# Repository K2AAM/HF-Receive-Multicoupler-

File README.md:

# HF Receive Multicoupler — Rev B

One antenna (an active receive loop such as the LZ1AQ AAA-1C or W6LVP) feeding four receivers: an RX888 or RSPdx plus vintage communications receivers. Four ports, through-hole, no hand-wound transformers, 13.8 V supply.

**Status:** design, simulation and a first prototype PCB layout (build A, branch `prototype-pcb`). Nothing here has been built or measured yet. All performance numbers are ngspice simulations with approximate transistor models. Treat them as estimates until the hardware is measured. The second verification pass ([`docs/review2-response.md`](docs/review2-response.md)) lists what is supported, what is not, and what needs bench work.

## Simulated performance, build A (recommended)

Conditions: 50 Ω source, four 50 Ω loads, measured at J2. Nominal parts, 9.81 V rail.

| Parameter | 1 MHz | 7–10 MHz | 28–30 MHz | 50 MHz |
| --- | --- | --- | --- | --- |
| Gain (dB) | +1.72 | +1.69 | +1.42 | +0.84 |
| Port-to-port isolation (dB) | 34.2 | 34.0 | 32.3 | 29.4 |
| Output-to-input isolation (dB) | 107 | 80 | 61 | 52 |
| NF (dB, excludes the receiver's own load noise) | 8.2 | 8.3 | 9.2 | 10.6 |
| IIP3 (dBm, −10 dBm tones) | +32.0 | +30.9 (7 MHz) | +27.1 (28 MHz) | — |

**Other figures:**

- **Flatness:** 0.88 dB from 10 kHz to 50 MHz (gain 1.72 dB at 10 kHz down to 0.84 dB at 50 MHz); 0.3 dB to 30 MHz.
- **Match:** S11 ≤ −23.3 dB and S22 ≤ −23.3 dB from 10 kHz to 50 MHz.
- **FM rejection:** 34.8 dB at 88 MHz, 44.8 dB at 100 MHz, 50.7 dB at 108 MHz.
- **IIP2:** about +79 dBm (6 + 7 MHz) and +79 to +82 dBm (0.6 + 1.0 MHz).
- **Output P1dB:** +11.7 dBm at 7 MHz.
- **Supply:** 95 mA from 13.8 V.

**Tolerance spread** (200-run Monte Carlo, every part independent, published tolerances, LPF inductors VNA-selected to ±3 %):

- gain at 1 MHz: 1.54–1.89 dB
- gain at 50 MHz: 0.69–1.04 dB
- flatness, 10 kHz–50 MHz: 0.79–0.91 dB
- worst S11: −19.4 dB (about −19.2 dB with the stocked ±5 % 43 pF end capacitors now in the BOM)
- rejection at 88 MHz: 33.4–35.8 dB
- NF at 10 MHz: 8.1–9.1 dB
- IIP3 at 7 MHz: +29.1 to +31.8 dBm
- IIP2: +60 to +88 dBm (depends on NPN/PNP matching)
- rail current: 79–97 mA

**If you skip inductor selection,** expect S11 as poor as about −11 dB, flatness up to ~1.3 dB and 88 MHz rejection down to ~31 dB.

All band-edge and named-frequency values come from exact single-frequency solves, not from the nearest sweep point (see section 0 of the review 2 response).

Builds B (+3.2 dB) and C (+5.5 dB) are in [`sim/results/summary.json`](sim/results/summary.json). Build C loses intercept quickly with signals near 0 dBm.

## Prototype PCB (build A)

- **Board:** 2 layers, through-hole, 104 × 78 mm, for a Hammond 1590C.
- **Connectors:** four R/A PCB BNC outputs on the front wall; input BNC on the left wall and DC jack on the back wall, both panel-mounted.
- **Checks:** DRC is clean, and the schematic, PCB and simulation netlists agree pin for pin. KiCad's own ERC still needs one run in eeschema (KiCad 7 has no command-line ERC).
- **Layout-parasitic estimate (simulated):** with the estimated trace capacitance, worst S11 moves from −23 dB to about −18 dB. The gain response barely moves.
- **Before ordering:** the enclosure dimensions and connector panel cut-outs still need checking on real parts.

Details: [`docs/pcb-prototype-A.md`](docs/pcb-prototype-A.md).

## Repository layout

| Path | Contents |
| --- | --- |
| `hardware/` | Schematic (`schematic_revB.png/.svg`, generated by `sch_revb.py`); sourced BOM (`BOM_revB.csv`) |
| `docs/review2-response.md` | Current verification status (supersedes parts of `review-response.md`) |
| `docs/bringup-and-test.md` | Inductor selection, power-only test with dummy load, bring-up and bench tests |
| `docs/layout-guidance.md` | PCB layout rules |
| `docs/pcb-prototype-A.md` | Prototype PCB (build A): part and footprint choices, layout, checks done, Hammond 1590C fit and drilling, layout-parasitic estimate, open items before ordering |
| `hardware/kicad/` | KiCad 7 project (schematic, PCB, footprint library), Gerbers and drill, BOM with MPNs and footprints, board and enclosure images, generator and check scripts |
| `sim/scripts/gen.py` | Single netlist generator; builds A/B/C in `BUILDS`; checked simulation runner |
| `sim/spice/*.cir` | Standalone decks for build A (exported by `export_netlists.py`) |
| `sim/results/` | All generated results |

## Running the simulations

Requires ngspice 42 or later and Python 3 with numpy and matplotlib. Run from `sim/scripts`:

```
python3 test_harness.py       # 26 regression checks: failure handling + exact-frequency sampling
python3 run_all.py            # builds A, B, C: op, AC, NF, IP3/IP2 (80 and 160 steps), P1dB -> summary.json
python3 convergence.py        # two-tone timestep / reltol / method study
python3 mc.py 200 200         # Monte Carlo + corners -> mc_A.json
python3 lpf_study.py 100      # LPF tolerance options
python3 stability.py A        # 5-port S-matrix mu test + 33 cable-kick cases (also B, C); then mu_bands.py A
python3 supply.py             # start-up, headroom, rail impedance, ripple bound, fault, dummy load
python3 freq_density.py       # passband extrema vs sweep density (25-400 points/decade)
python3 thermal.py; python3 export_netlists.py; python3 plot.py
```

Every run uses its own temporary directory and is rejected on any of these:

- non-zero exit
- simulator error text
- missing completion marker
- a missing, stale, empty, non-finite or truncated output

Failures are counted and reported, never skipped.

**Name map** (generator → schematic): CIN1 = C1, CBN/CBP = C2/C3, CF1–CF4 = C4–C7, LF1–LF3 = L1–L3, CFB = C8, CLX = C9, RLX = RL, REO1/REO2 = RE3/RE4, RCOL = RC, CO1–CO4 = C10–C13, CRM/CRMP = C14/C15, CU1O = C23.

## Model limits

- **Transistor models:** 2N3904/2N3906 are simplified Gummel-Poon models from the LTspice library. Absolute IP3/IP2 can differ from hardware by several dB, and IP2 depends on device matching.
- **50 MHz gain:** depends on the real collector capacitance. With CJC 40 % higher than modelled, gain at 50 MHz drops to +0.33 dB (1.39 dB flatness).
- **Regulator model:** the LM317 is behavioural, with ideal line rejection and typical dropout.
- **Stability:** checked to 2 GHz with lumped parasitics. The models are unreliable above ~500 MHz, so a hardware oscillation check is required.

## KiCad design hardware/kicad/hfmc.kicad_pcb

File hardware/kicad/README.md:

# KiCad project: prototype PCB, build A

The design description, the check results and the open items are in [`docs/pcb-prototype-A.md`](../../docs/pcb-prototype-A.md).

**Native files:**

| File | What it is |
| --- | --- |
| `hfmc.kicad_pro` | Project |
| `hfmc.kicad_sch` | Schematic |
| `hfmc.kicad_pcb` | PCB |
| `fp-lib-table` + `hfmc.pretty/` | Project footprint library (BNC, thermal-pair TO-92, GDT, KEMET C320, universal C32x, RXEF, pigtail and wire pads) |

The files were made with KiCad 7.0.11 and open in KiCad 7 or later.

**Outputs:**

| File | Contents |
| --- | --- |
| `hfmc_schematic.pdf` | Schematic |
| `hfmc_gerbers.zip` | Gerbers + Excellon drill, the upload for OSH Park |
| `fab/` | The same files loose, plus a drill map |
| `img/` | Board and enclosure-fit views |
| `BOM_prototype_A.csv` | Bill of materials |

## How the files are produced

`design.py` is the single source of truth: parts, values, MPNs, footprints, and pin-to-net maps whose net names are the `sim/scripts/gen.py` node names. Everything else is generated from it.

| Step | Command | Notes |
| --- | --- | --- |
| Footprints | `python3 mkfp.py` | Writes `hfmc.pretty/` |
| Schematic | `python3 make_sch.py` | Then `kicad-cli sch export netlist -o hfmc.net hfmc.kicad_sch` |
| Placement | `place.py` | Hand placement, merged with `place_core.json`, which comes from `autoplace_core.py` (core annealer: `/usr/bin/python3 autoplace_core.py <seed> place_core.json 200000 <T0>`) |
| Board, routing, pours, DRC | `./run_all.sh` | Needs KiCad's python (`/usr/bin/python3` with `pcbnew`), Java, `xvfb-run` and `freerouting.jar` (Freerouting 1.9.0 from GitHub releases; not committed) |
| Fab outputs, images, enclosure views | `./make_outputs.sh` | Then `python3 make_bom.py` for the BOM |

**What `run_all.sh` does:**

1. Builds the board.
2. Routes in two Freerouting passes:
   - Pass 1 declares B.Cu a plane, so signals go on F.Cu.
   - Pass 2 lets B.Cu finish only what is left.
3. Imports the routing (`ses_import.py`).
4. Adds GND pours on both layers and makes starved GND pads solid.
5. Adds stitching vias and places the silkscreen references.
6. Runs DRC.

**Freerouting is not deterministic.** Each run gives a different routing. The committed `hfmc.kicad_pcb` is the routing that all the checks below were run on. If you re-run `run_all.sh`, run the checks again.

## Checks

| Command | Checks | Report |
| --- | --- | --- |
| `/usr/bin/python3 check_conn.py` | Simulation netlist ↔ schematic ↔ PCB pads, plus pin functions | `check_conn.txt` |
| `python3 erc_check.py` | Scripted ERC on the exported netlist | `erc_check.txt` |
| `/usr/bin/python3 drc.py hfmc.kicad_pcb drc.rpt` | KiCad DRC | `drc.rpt` |
| `python3 check_place.py` | Courtyard overlaps | `check_place.txt` |
| `/usr/bin/python3 layout_report.py` | Branch lengths, bypass distances, LPF geometry | `layout_report.json` |
| `/usr/bin/python3 enclosure.py` | Hammond 1590C fit, insertion path and drilling. Each value is tagged MFR / DWG / CALC / ASSUME | `enclosure_report.txt`, `enclosure.json`, `img/enclosure_*.png`, `img/drill_*.png`, `drill_drawing_1590C.pdf` |
| `bash erc_native.sh` | KiCad 7 eeschema native ERC, driven under Xvfb with xdotool (KiCad 7 has no CLI ERC) | `erc_native.rpt`, `erc_native.png` |
| `/usr/bin/python3 layout_parasitics.py` | Estimated trace capacitance added to the build-A simulation (needs ngspice) | `layout_parasitics.json` |

To run headless, set `KICAD7_FOOTPRINT_DIR=/usr/share/kicad/footprints`.

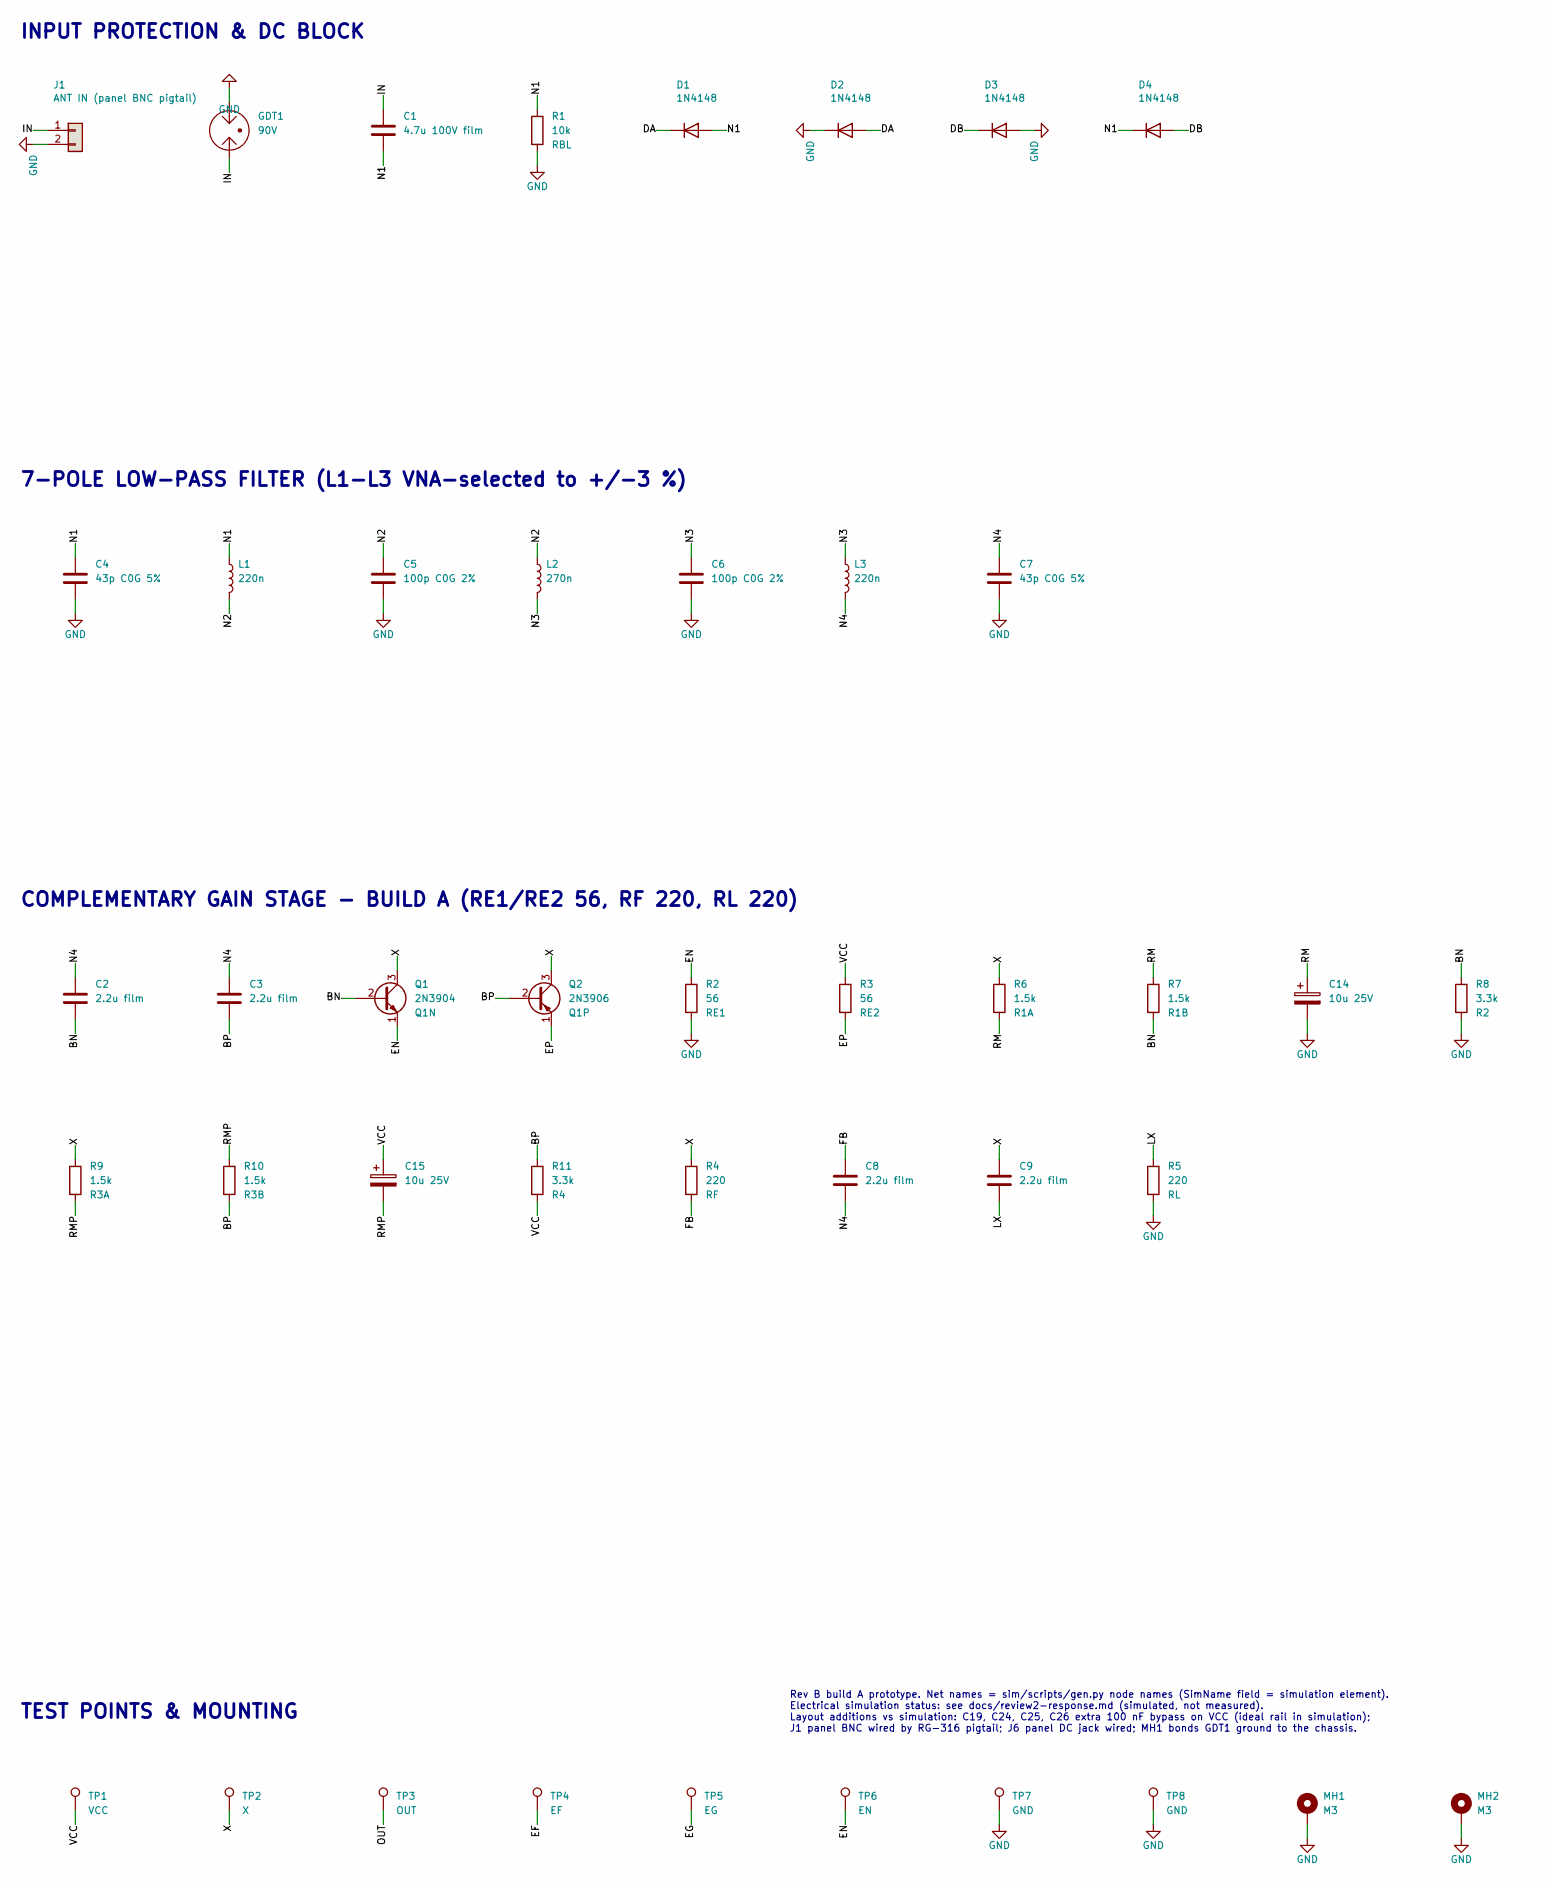
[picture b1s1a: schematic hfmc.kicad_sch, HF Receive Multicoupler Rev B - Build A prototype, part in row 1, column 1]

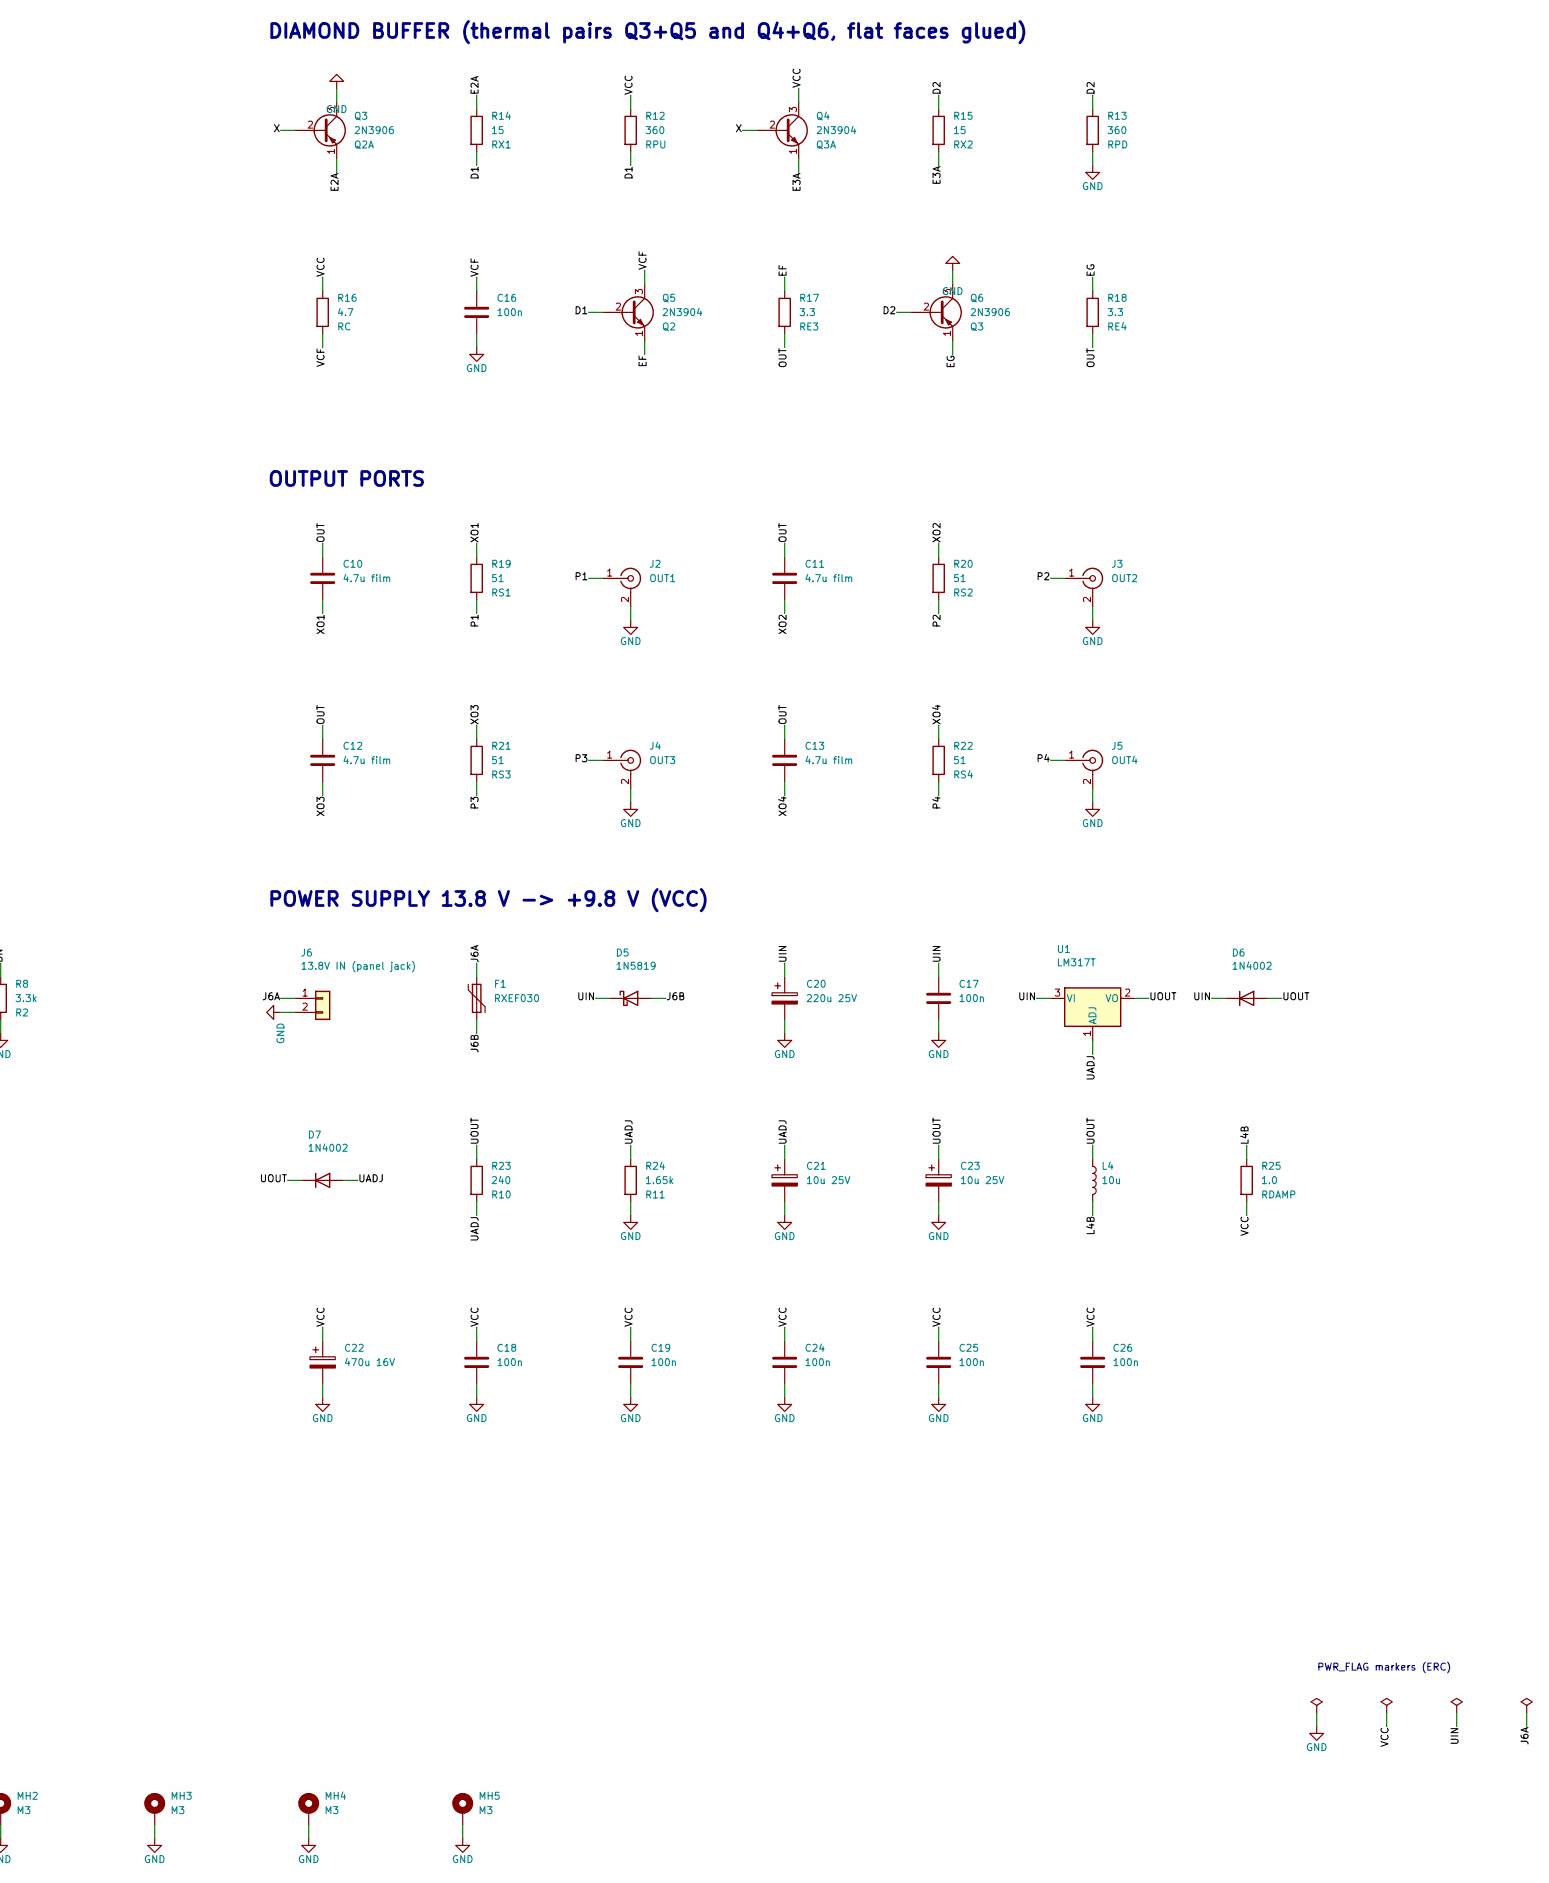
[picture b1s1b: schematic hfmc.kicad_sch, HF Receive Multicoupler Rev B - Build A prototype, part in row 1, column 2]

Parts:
C1: 4.7u 100V film; C_Rect_L18.0mm_W11.0mm_P15.00mm_FKS3_FKP3; MPN KEMET R60EI4470AA30J
C2, C3, C8, C9: 2.2u film; C_Rect_L7.2mm_W7.2mm_P5.00mm_FKS2_FKP2_MKS2_MKP2; MPN KEMET R82CC4220DQ70J
C4, C7: 43p C0G 5%; C_Disc_W3.2mm_P2.54mm_P5.08mm_Universal; MPN KEMET C325C430JAG5TA
C5, C6: 100p C0G 2%; C_Disc_D3.8mm_W2.6mm_P2.50mm; MPN KEMET C315C101G1G5TA
C10, C11, C12, C13: 4.7u film; C_Rect_L7.2mm_W7.2mm_P5.00mm_FKS2_FKP2_MKS2_MKP2; MPN KEMET R82CC4470DQ30K
C14, C15, C21, C23: 10u 25V; CP_Radial_D5.0mm_P2.00mm; MPN Panasonic ECA-1EM100
C16, C17, C18, C19, C24, C25, C26: 100n; C_Radial_KEMET_C320_L5.08mm_T3.18mm_P2.54mm; MPN KEMET C320C104K5R5TA
C20: 220u 25V; CP_Radial_D8.0mm_P3.50mm; MPN Panasonic EEU-FR1E221
C22: 470u 16V; CP_Radial_D8.0mm_P3.50mm; MPN Panasonic EEU-FR1C471
D1, D2, D3, D4: 1N4148; D_DO-35_SOD27_P7.62mm_Horizontal; MPN onsemi 1N4148
D5: 1N5819; D_DO-41_SOD81_P10.16mm_Horizontal; MPN onsemi 1N5819
D6, D7: 1N4002; D_DO-41_SOD81_P10.16mm_Horizontal; MPN onsemi 1N4002
F1: RXEF030; Fuse_Littelfuse_RXEF_7.4x3.0mm_P5.10mm; MPN Littelfuse RXEF030
GDT1: 90V; GDT_Bourns_2027_Axial_D8.0mm_L6.0mm_P12.70mm_Horizontal; MPN Bourns 2027-09-BLF
J1: ANT IN (panel BNC pigtail); Pads_CoaxPigtail_RG316; MPN Amphenol RF 031-221-RFX (panel BNC, wir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
J2: OUT1; BNC_Amphenol_031-5431-10RFX_Horizontal; MPN Amphenol RF 031-5431-10RFX
J3: OUT2; BNC_Amphenol_031-5431-10RFX_Horizontal; MPN Amphenol RF 031-5431-10RFX
J4: OUT3; BNC_Amphenol_031-5431-10RFX_Horizontal; MPN Amphenol RF 031-5431-10RFX
J5: OUT4; BNC_Amphenol_031-5431-10RFX_Horizontal; MPN Amphenol RF 031-5431-10RFX
J6: 13.8V IN (panel jack); Pads_PowerWire_1x02_P5.08mm; MPN Switchcraft 722A (2.1 mm panel jack, ce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
L1, L3: 220n; L_Axial_L7.0mm_D3.3mm_P10.16mm_Horizontal_Fastron_MICC; MPN Bourns 78FR22K-RC (VNA-selected +/-3%)
L2: 270n; L_Axial_L7.0mm_D3.3mm_P10.16mm_Horizontal_Fastron_MICC; MPN Bourns 78FR27K-RC (VNA-selected +/-3%)
L4: 10u; L_Radial_D9.5mm_P5.00mm_Fastron_07HVP; MPN Bourns RLB0914-100KL
MH1, MH2, MH3, MH4, MH5: M3; MountingHole_3.2mm_M3_Pad_Via; MPN Wurth 970060354 (M3 x 6 mm brass hex sp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
Q1: 2N3904; TO-92_Inline; MPN onsemi 2N3904BU
Q2: 2N3906; TO-92_Inline; MPN onsemi 2N3906BU
Q3, Q6: 2N3906; TO-92_Inline_ThermalPair; MPN onsemi 2N3906BU
Q4, Q5: 2N3904; TO-92_Inline_ThermalPair; MPN onsemi 2N3904BU
R1: 10k; R_Axial_DIN0207_L6.3mm_D2.5mm_P7.62mm_Horizontal; MPN Yageo MFR-25FBF52-10K
R2, R3: 56; R_Axial_DIN0207_L6.3mm_D2.5mm_P7.62mm_Horizontal; MPN Yageo MFR-25FBF52-56R
R4, R5: 220; R_Axial_DIN0207_L6.3mm_D2.5mm_P7.62mm_Horizontal; MPN Yageo MFR-25FBF52-220R
R6, R7, R9, R10: 1.5k; R_Axial_DIN0207_L6.3mm_D2.5mm_P7.62mm_Horizontal; MPN Yageo MFR-25FBF52-1K5
R8, R11: 3.3k; R_Axial_DIN0207_L6.3mm_D2.5mm_P7.62mm_Horizontal; MPN Yageo MFR-25FBF52-3K3
R12, R13: 360; R_Axial_DIN0207_L6.3mm_D2.5mm_P7.62mm_Horizontal; MPN Yageo MFR-25FBF52-360R
R14, R15: 15; R_Axial_DIN0207_L6.3mm_D2.5mm_P7.62mm_Horizontal; MPN Yageo MFR-25FBF52-15R
R16: 4.7; R_Axial_DIN0207_L6.3mm_D2.5mm_P7.62mm_Horizontal; MPN Yageo MFR-25FBF52-4R7
R17, R18: 3.3; R_Axial_DIN0207_L6.3mm_D2.5mm_P7.62mm_Horizontal; MPN Yageo MFR-25FBF52-3R3
R19, R20, R21, R22: 51; R_Axial_DIN0207_L6.3mm_D2.5mm_P7.62mm_Horizontal; MPN Yageo MFR-25FBF52-51R
R23: 240; R_Axial_DIN0207_L6.3mm_D2.5mm_P7.62mm_Horizontal; MPN Yageo MFR-25FBF52-240R
R24: 1.65k; R_Axial_DIN0207_L6.3mm_D2.5mm_P7.62mm_Horizontal; MPN Yageo MFR-25FBF52-1K65
R25: 1.0; R_Axial_DIN0207_L6.3mm_D2.5mm_P7.62mm_Horizontal; MPN Yageo MFR-25FBF52-1R
TP1: VCC; TestPoint_Keystone_5000-5004_Miniature; MPN Keystone 5000
TP2: X; TestPoint_Keystone_5000-5004_Miniature; MPN Keystone 5000
TP3: OUT; TestPoint_Keystone_5000-5004_Miniature; MPN Keystone 5000
TP4: EF; TestPoint_Keystone_5000-5004_Miniature; MPN Keystone 5000
TP5: EG; TestPoint_Keystone_5000-5004_Miniature; MPN Keystone 5000
TP6: EN; TestPoint_Keystone_5000-5004_Miniature; MPN Keystone 5000
TP7, TP8: GND; TestPoint_Keystone_5000-5004_Miniature; MPN Keystone 5001
U1: LM317T; TO-220-3_Horizontal_TabDown; MPN TI LM317T/NOPB

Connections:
BN: C2.2, Q1.2 (B), R7.2, R8.1
BP: C3.2, Q2.2 (B), R10.2, R11.1
D1: Q5.2 (B), R12.2, R14.2
D2: Q6.2 (B), R13.1, R15.1
DA: D1.1 (K), D2.2 (A)
DB: D3.1 (K), D4.2 (A)
E2A: Q3.1 (E), R14.1
E3A: Q4.1 (E), R15.2
EF: Q5.1 (E), R17.1, TP4.1
EG: Q6.1 (E), R18.1, TP5.1
EN: Q1.1 (E), R2.1, TP6.1
EP: Q2.1 (E), R3.2
FB: C8.1, R4.2
GND: C4.2, C5.2, C6.2, C7.2, C14.2, C16.2, C17.2, C18.2, C19.2, C20.2, C21.2, C22.2, C23.2, C24.2, C25.2, C26.2, D2.1 (K), D3.2 (A), GDT1.3, J1.2, J2.2 (Ext), J3.2 (Ext), J4.2 (Ext), J5.2 (Ext), J6.2, MH1.1, MH2.1, MH3.1, MH4.1, MH5.1, Q3.3 (C), Q6.3 (C), R1.2, R2.2, R5.2, R8.2, R13.2, R24.2, TP7.1, TP8.1
IN: C1.1, GDT1.1, J1.1
J6A: F1.1, J6.1
J6B: D5.2 (A), F1.2
L4B: L4.2, R25.1
LX: C9.2, R5.1
N1: C1.2, C4.1, D1.2 (A), D4.1 (K), L1.1, R1.1
N2: C5.1, L1.2, L2.1
N3: C6.1, L2.2, L3.1
N4: C2.1, C3.1, C7.1, C8.2, L3.2
OUT: C10.1, C11.1, C12.1, C13.1, R17.2, R18.2, TP3.1
P1: J2.1 (In), R19.2
P2: J3.1 (In), R20.2
P3: J4.1 (In), R21.2
P4: J5.1 (In), R22.2
RM: C14.1, R6.2, R7.1
RMP: C15.2, R9.2, R10.1
UADJ: C21.1, D7.2 (A), R23.2, R24.1, U1.1 (ADJ)
UIN: C17.1, C20.1, D5.1 (K), D6.1 (K), U1.3 (VI)
UOUT: C23.1, D6.2 (A), D7.1 (K), L4.1, R23.1, U1.2 (VO)
VCC: C15.1, C18.1, C19.1, C22.1, C24.1, C25.1, C26.1, Q4.3 (C), R3.1, R11.2, R12.1, R16.1, R25.2, TP1.1
VCF: C16.1, Q5.3 (C), R16.2
X: C9.1, Q1.3 (C), Q2.3 (C), Q3.2 (B), Q4.2 (B), R4.1, R6.1, R9.1, TP2.1
XO1: C10.2, R19.1
XO2: C11.2, R20.1
XO3: C12.2, R21.1
XO4: C13.2, R22.1

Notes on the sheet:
INPUT PROTECTION & DC BLOCK
7-POLE LOW-PASS FILTER (L1-L3 VNA-selected to +/-3 %)
COMPLEMENTARY GAIN STAGE - BUILD A (RE1/RE2 56, RF 220, RL 220)
DIAMOND BUFFER (thermal pairs Q3+Q5 and Q4+Q6, flat faces glued)
OUTPUT PORTS
POWER SUPPLY 13.8 V -> +9.8 V (VCC)
TEST POINTS & MOUNTING
PWR_FLAG markers (ERC)
Rev B build A prototype. Net names = sim/scripts/gen.py node names (SimName field = simulation element). Electrical simulation status: see docs/review2-response.md (simulated, not measured). Layout additions vs simulation: C19, C24, C25, C26 extra 100 nF bypass on VCC (ideal rail in simulation); J1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

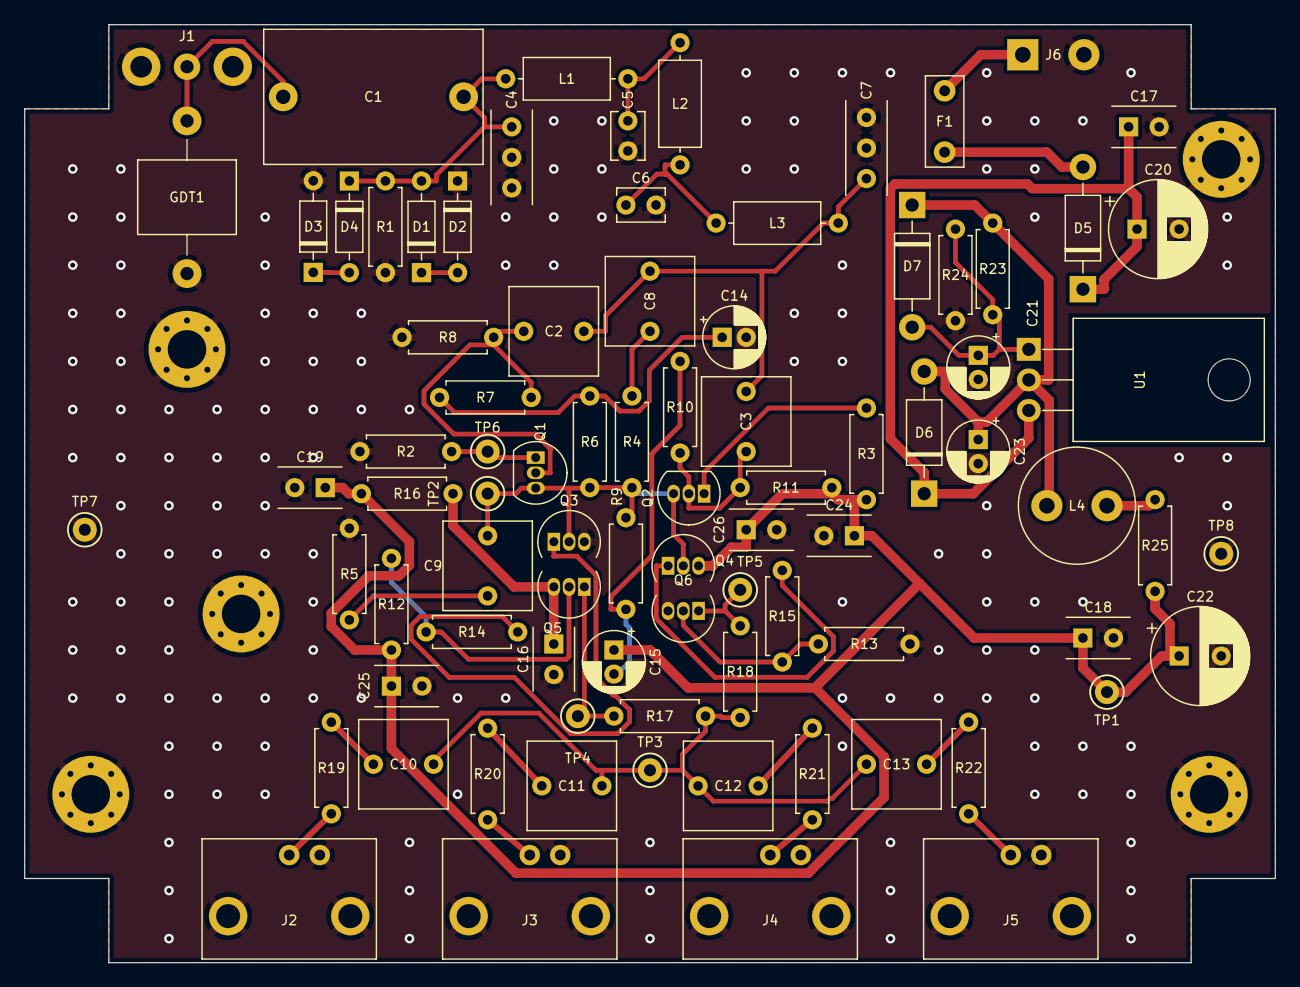
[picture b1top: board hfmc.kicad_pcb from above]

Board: 2 copper layers, 104.0 x 78.0 mm, 90 parts (0 on the bottom side), 40 nets.

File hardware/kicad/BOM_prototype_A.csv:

KiCad refs,Doc/sim refs (if different),Qty,Value,Manufacturer part,KiCad footprint,Body / pitch (from datasheet),Notes
C1,,1,4.7u 100V film,KEMET R60EI4470AA30J,Capacitor_THT:C_Rect_L18.0mm_W11.0mm_P15.00mm_FKS3_FKP3,"18 x 11 x 19.1 mm, 15 mm pitch","18x11x19.1 mm, 15 mm pitch"
C2 C3 C8 C9,,4,2.2u film,KEMET R82CC4220DQ70J,Capacitor_THT:C_Rect_L7.2mm_W7.2mm_P5.00mm_FKS2_FKP2_MKS2_MKP2,"7.2 x 6 x 11 mm, 5 mm pitch",
C4 C7,,2,43p C0G 5%,KEMET C325C430JAG5TA,hfmc:C_Disc_W3.2mm_P2.54mm_P5.08mm_Universal,"5.08 x 3.18, H 7.62 max, 2.54 or 5.08 mm",
C5 C6,,2,100p C0G 2%,KEMET C315C101G1G5TA,Capacitor_THT:C_Disc_D3.8mm_W2.6mm_P2.50mm,"3.81 x 2.54, H 4.66 max, 2.54 mm",
C10 C11 C12 C13,,4,4.7u film,KEMET R82CC4470DQ30K,Capacitor_THT:C_Rect_L7.2mm_W7.2mm_P5.00mm_FKS2_FKP2_MKS2_MKP2,"7.2 x 7.2 x 13 mm, 5 mm pitch",
C14 C15 C21 C23,,4,10u 25V,Panasonic ECA-1EM100,Capacitor_THT:CP_Radial_D5.0mm_P2.00mm,"5 x 11, 2 mm pitch",+ to RM; + to VCC; U1 output cap (CU1O)
C16 C17 C18 C19 C24 C25 C26,,7,100n,KEMET C320C104K5R5TA,hfmc:C_Radial_KEMET_C320_L5.08mm_T3.18mm_P2.54mm,"5.08 x 3.18, H 7.36 max, 2.54 mm",Local bypass at Q3A collector; Local bypass at RE2/R4/C15; Local bypass at RPU; Local bypass rail entry to amplifier
C20,,1,220u 25V,Panasonic EEU-FR1E221,Capacitor_THT:CP_Radial_D8.0mm_P3.50mm,"8 x 11.5, 3.5 mm pitch",
C22,,1,470u 16V,Panasonic EEU-FR1C471,Capacitor_THT:CP_Radial_D8.0mm_P3.50mm,"8 x 11.5, 3.5 mm pitch",
D1 D2 D3 D4,,4,1N4148,onsemi 1N4148,Diode_THT:D_DO-35_SOD27_P7.62mm_Horizontal,,
D5,,1,1N5819,onsemi 1N5819,Diode_THT:D_DO-41_SOD81_P10.16mm_Horizontal,,
D6 D7,,2,1N4002,onsemi 1N4002,Diode_THT:D_DO-41_SOD81_P10.16mm_Horizontal,,
F1,,1,RXEF030,Littelfuse RXEF030,hfmc:Fuse_Littelfuse_RXEF_7.4x3.0mm_P5.10mm,"7.4 x 3.0, H 12.7 max, 5.1 mm",
GDT1,,1,90V,Bourns 2027-09-BLF,hfmc:GDT_Bourns_2027_Axial_D8.0mm_L6.0mm_P12.70mm_Horizontal,8 dia x 6 axial,Ground pad bonded to MH1 (chassis) by a short wide pour
J1,,1,ANT IN (panel BNC pigtail),"Amphenol RF 031-221-RFX (panel BNC, wired with ~60 mm RG-316)",hfmc:Pads_CoaxPigtail_RG316,,"Panel jack on the left end wall of the Hammond 1590C (see docs/pcb-prototype-A.md); RG-316 pigtail to these pads, braid to both GND pads"
J2,,1,OUT1,Amphenol RF 031-5431-10RFX,hfmc:BNC_Amphenol_031-5431-10RFX_Horizontal,"R/A PCB bulkhead, rear mount",
J3,,1,OUT2,Amphenol RF 031-5431-10RFX,hfmc:BNC_Amphenol_031-5431-10RFX_Horizontal,"R/A PCB bulkhead, rear mount",
J4,,1,OUT3,Amphenol RF 031-5431-10RFX,hfmc:BNC_Amphenol_031-5431-10RFX_Horizontal,"R/A PCB bulkhead, rear mount",
J5,,1,OUT4,Amphenol RF 031-5431-10RFX,hfmc:BNC_Amphenol_031-5431-10RFX_Horizontal,"R/A PCB bulkhead, rear mount",
J6,,1,13.8V IN (panel jack),"Switchcraft 722A (2.1 mm panel jack, centre +)",hfmc:Pads_PowerWire_1x02_P5.08mm,,Wired to the back-wall jack
L1 L3,,2,220n,Bourns 78FR22K-RC (VNA-selected +/-3%),Inductor_THT:L_Axial_L7.0mm_D3.3mm_P10.16mm_Horizontal_Fastron_MICC,,
L2,,1,270n,Bourns 78FR27K-RC (VNA-selected +/-3%),Inductor_THT:L_Axial_L7.0mm_D3.3mm_P10.16mm_Horizontal_Fastron_MICC,,
L4,,1,10u,Bourns RLB0914-100KL,Inductor_THT:L_Radial_D9.5mm_P5.00mm_Fastron_07HVP,"8.7 dia x 13 mm max, 5 mm pitch",
Q1,Q1N,1,2N3904,onsemi 2N3904BU,Package_TO_SOT_THT:TO-92_Inline,,
Q2,Q1P,1,2N3906,onsemi 2N3906BU,Package_TO_SOT_THT:TO-92_Inline,,
Q3 Q6,Q2A Q3,2,2N3906,onsemi 2N3906BU,hfmc:TO-92_Inline_ThermalPair,,Thermal pair: glue flat face to Q4 (doc Q3A); Thermal pair: glue flat face to Q5 (doc Q2)
Q4 Q5,Q3A Q2,2,2N3904,onsemi 2N3904BU,hfmc:TO-92_Inline_ThermalPair,,Thermal pair: glue flat face to Q3 (doc Q2A); Thermal pair: glue flat face to Q6 (doc Q3)
R1,RBL,1,10k,Yageo MFR-25FBF52-10K,Resistor_THT:R_Axial_DIN0207_L6.3mm_D2.5mm_P7.62mm_Horizontal,,
R2 R3,RE1 RE2,2,56,Yageo MFR-25FBF52-56R,Resistor_THT:R_Axial_DIN0207_L6.3mm_D2.5mm_P7.62mm_Horizontal,,"Build A 56 (B 56, C 47)"
R4 R5,RF RL,2,220,Yageo MFR-25FBF52-220R,Resistor_THT:R_Axial_DIN0207_L6.3mm_D2.5mm_P7.62mm_Horizontal,,"Build A 220 (B 270, C 330); RLX, all builds"
R6 R7 R9 R10,R1A R1B R3A R3B,4,1.5k,Yageo MFR-25FBF52-1K5,Resistor_THT:R_Axial_DIN0207_L6.3mm_D2.5mm_P7.62mm_Horizontal,,
R8 R11,R2 R4,2,3.3k,Yageo MFR-25FBF52-3K3,Resistor_THT:R_Axial_DIN0207_L6.3mm_D2.5mm_P7.62mm_Horizontal,,
R12 R13,RPU RPD,2,360,Yageo MFR-25FBF52-360R,Resistor_THT:R_Axial_DIN0207_L6.3mm_D2.5mm_P7.62mm_Horizontal,,
R14 R15,RX1 RX2,2,15,Yageo MFR-25FBF52-15R,Resistor_THT:R_Axial_DIN0207_L6.3mm_D2.5mm_P7.62mm_Horizontal,,
R16,RC,1,4.7,Yageo MFR-25FBF52-4R7,Resistor_THT:R_Axial_DIN0207_L6.3mm_D2.5mm_P7.62mm_Horizontal,,
R17 R18,RE3 RE4,2,3.3,Yageo MFR-25FBF52-3R3,Resistor_THT:R_Axial_DIN0207_L6.3mm_D2.5mm_P7.62mm_Horizontal,,
R19 R20 R21 R22,RS1 RS2 RS3 RS4,4,51,Yageo MFR-25FBF52-51R,Resistor_THT:R_Axial_DIN0207_L6.3mm_D2.5mm_P7.62mm_Horizontal,,
R23,R10,1,240,Yageo MFR-25FBF52-240R,Resistor_THT:R_Axial_DIN0207_L6.3mm_D2.5mm_P7.62mm_Horizontal,,
R24,R11,1,1.65k,Yageo MFR-25FBF52-1K65,Resistor_THT:R_Axial_DIN0207_L6.3mm_D2.5mm_P7.62mm_Horizontal,,
R25,RDAMP,1,1.0,Yageo MFR-25FBF52-1R,Resistor_THT:R_Axial_DIN0207_L6.3mm_D2.5mm_P7.62mm_Horizontal,,
TP1,,1,VCC,Keystone 5000,TestPoint:TestPoint_Keystone_5000-5004_Miniature,,+9.8 V rail
TP2,,1,X,Keystone 5000,TestPoint:TestPoint_Keystone_5000-5004_Miniature,,gain-stage collector node X
TP3,,1,OUT,Keystone 5000,TestPoint:TestPoint_Keystone_5000-5004_Miniature,,common output node
TP4,,1,EF,Keystone 5000,TestPoint:TestPoint_Keystone_5000-5004_Miniature,,RE3 top: I(Q2) = V(TP4-TP3)/3.3
TP5,,1,EG,Keystone 5000,TestPoint:TestPoint_Keystone_5000-5004_Miniature,,RE4 bottom: I(Q3) = V(TP3-TP5)/3.3
TP6,,1,EN,Keystone 5000,TestPoint:TestPoint_Keystone_5000-5004_Miniature,,RE1 top: I(Q1N) = V(TP6)/56
TP7 TP8,,2,GND,Keystone 5001,TestPoint:TestPoint_Keystone_5000-5004_Miniature,,ground
U1,,1,LM317T,TI LM317T/NOPB,Package_TO_SOT_THT:TO-220-3_Horizontal_TabDown,,"Lies flat, tab down on solder mask over a copper keep-out (tab = VOUT); optional M3 nylon screw, no heatsink"
(J1 panel),,1,"BNC jack, front-mount bulkhead",Amphenol RF 031-221-RFX,"panel, left end wall","27.0 mm long, 12.7 hex nut, max panel 3.2","Input connector; RG-316 pigtail to J1 pads. D-hole 11.1 / 10.3 flat (Amphenol type U, confirm on drawing). Fit after the PCB"
(J1 cable),,1,"RG-316 coax, ~60 mm",any RG-316 (e.g. Belden 83284),,,"Centre to J1 pad 1, braid to J1 pads 2"
(J6 panel),,1,DC power jack 2.1 mm (2.0 mm pin),Switchcraft 722A,"panel, back wall","20.8 mm long, 5/16-32 bushing, solder lugs","Centre positive. Wire to J6 pads (1 = +13.8 V, 2 = GND). D-hole 8.00 / 7.37 flat (confirm on drawing). Fit after the PCB"
MH1-MH5,,5,"M3 x 6 mm hex spacer, brass, female-female, 5 mm hex",Wurth 970060354,MountingHole_3.2mm_M3_Pad_Via,,Bonds board GND to the box floor at every hole
MH1-MH5,,10,"M3 x 5 pan-head screw, stainless",any ISO 7045 M3 x 5,,,"5 on top through the PCB, 5 from below through the dia 4.2 floor holes"
MH1-MH5,,10,M3 flat washer (DIN 125 3.2),any,,,Under each screw head; the floor ones bridge the oversize holes
J2-J5,,4,"M12 flat washer, steel, ID 13 / OD 20 / t 2 (DIN 433)",any DIN 433 M12 zinc-plated,,,"Outside, under the supplied lock washer and nut: bridges the 12.9 x 15.5 wall slot"
"Q3/Q5, Q4/Q6","Q2A/Q2, Q3A/Q3",1,thermally conductive epoxy or cyanoacrylate + heat-shrink,e.g. Arctic Silver thermal adhesive,,,Glue the flat faces of each pair together
U1,,1,M3 x 8 nylon screw + nut (optional),any nylon M3,,,Tab is VOUT; do not use a metal screw
Enclosure,,1,"Hammond 1590C die-cast aluminium, natural",Hammond 1590C,,119.5 x 94 x 56.5 mm with lid (inside 52.25 high),Machine and drill per hardware/kicad/drill_drawing_1590C.pdf; 1590CBK (black) needs the coating removed at spacer seats and BNC strips

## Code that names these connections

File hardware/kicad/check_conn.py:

"""Connectivity / pin-mapping check: simulation netlist (sim/scripts/gen.py, build A)
   vs KiCad schematic netlist (hfmc.net) vs PCB pad nets (hfmc.kicad_pcb).
   Run with KiCad's python (/usr/bin/python3); REPO env var points at the repo root."""
import os, re, sys, subprocess, json
REPO = os.environ.get("REPO", os.path.abspath(os.path.join(os.path.dirname(os.path.abspath(__file__)), "..", "..")))
sys.path.insert(0, os.path.join(REPO, "sim", "scripts"))
import gen
sys.path.insert(0, os.path.dirname(os.path.abspath(__file__)))
import design
fail = []
def bad(msg): fail.append(msg); print("FAIL", msg)

# ---------- 1. simulation netlist (build A, real supply, no parasitics)
P = gen.params("A"); P["PAR"] = False; P["SUPPLY"] = "real"
cir = gen.netlist(P, "op")
elems = {}
for ln in cir.splitlines():
    t = ln.split()
    if not t or t[0][0] in "*." or t[0].lower() in ("echo", "op", "run"): continue
    if t[0][0].upper() in "RCLDQVBI": elems[t[0]] = t[1:4] if t[0][0].upper() == "Q" else t[1:3]
WIRES = re.compile(r"^(RIN1|LIN1|RBNE|LBNE|RBPE|LBPE|LEN|LEP|LFB|LEF|LEG|RO\dE|LO\dE|LS\d|RLF\d|RL4DCR|R20E|R22E|RU1E|RSRC)$")
par = {}
def find(a):
    while par.get(a, a) != a: a = par[a]
    return a
def union(a, b):
    a, b = find(a), find(b)
    if a != b: par[max(a, b)] = min(a, b) if "0" not in (a, b) else "0"
for k, nodes in elems.items():
    if WIRES.match(k): union(*nodes[:2])
union("0", "0")
# behavioural LM317 internals: pass element from UIN to UPI, then RZU/LZU to UOUT (treat UPI..UOUT as U1 OUT)
for a, b in (("UPI", "UPJ"), ("UPJ", "UPK"), ("UPK", "UOUT")): union(a, b)
SN = lambda n: find(n)

# ---------- 2. sim element -> KiCad ref, and terminal order
SUPPLY = {"D5": "D5", "C20": "C20", "C20B": "C17", "D6": "D6", "D7": "D7", "R10": "R23", "R11": "R24",
          "C21": "C21", "CU1O": "C23", "L4": "L4", "RDMP": "R25", "C22": "C22", "C22B": "C18"}
bysim = {p["gen"]: p for p in design.P if p.get("gen")}
for s, r in SUPPLY.items():
    bysim[s] = next(p for p in design.P if p["ref"] == r)
def kpins(p, simname):
    pre = simname[0].upper()
    if pre == "Q": return ["3", "2", "1"]          # C, B, E  (onsemi TO-92: 1=E 2=B 3=C)
    if pre == "D": return ["2", "1"]               # anode, cathode (KiCad D: 1=K, 2=A)
    return ["1", "2"]

# ---------- 3. build node map sim->KiCad and check every mapped element
nmap = {SN("0"): "GND"}
checked = 0
for s, p in sorted(bysim.items()):
    if s not in elems: bad(f"{s}: in design.py but not in sim netlist"); continue
    snodes = [SN(n) for n in elems[s]]
    kp = kpins(p, s); knets = [p["pins"][k] for k in kp]
    pairs = list(zip(snodes, knets))
    if s[0].upper() in "RCL" and s not in ("C14", "C15", "C20", "C21", "C22", "CU1O", "CRM", "CRMP"):
        # unpolarised two-terminal: accept either orientation
        if not all(nmap.get(a, b) == b for a, b in pairs):
            pairs = list(zip(snodes, knets[::-1]))
    for a, b in pairs:
        if nmap.setdefault(a, b) != b: bad(f"{s}->{p['ref']}: sim node {a} maps to {nmap[a]} and {b}")
    checked += 1
inv = {}
for a, b in nmap.items():
    if inv.setdefault(b, a) != a: bad(f"KiCad net {b} corresponds to two sim nodes {inv[b]} and {a}")
print(f"sim elements checked against design: {checked}; node map size {len(nmap)}")

# U1 (behavioural model in sim): IN/OUT/ADJ by role
u1 = next(p for p in design.P if p["ref"] == "U1")
for pin, simnode in (("3", "UIN"), ("2", "UOUT"), ("1", "UADJ")):
    if nmap.get(SN(simnode)) != u1["pins"][pin]: bad(f"U1 pin {pin} net {u1['pins'][pin]} != sim {simnode}")

# ---------- 4. schematic netlist (kicad-cli export) vs design.py, incl. pin functions
txt = open("hfmc.net").read()
schnet = {}
pinfn = {}
for m in re.finditer(r'\(net \(code "\d+"\) \(name "([^"]+)"\)(.*?)\)\)\s*(?=\(net|\)\s*\)\s*$|$)', txt, re.S):
    name = m.group(1).lstrip("/")
    for r, pn, fn in re.findall(r'\(node \(ref "([^"]+)"\) \(pin "([^"]+)"\)(?: \(pinfunction "([^"]*)"\))?', m.group(2)):
        schnet[(r, pn)] = name; pinfn[(r, pn)] = fn
for p in design.P:
    for pn, n in p["pins"].items():
        if schnet.get((p["ref"], pn)) != n: bad(f"schematic {p['ref']}.{pn}: {schnet.get((p['ref'], pn))} != design {n}")
EXP = {"Q": {"1": "E", "2": "B", "3": "C"}, "D": {"1": "K", "2": "A"}, "U": {"1": "ADJ", "2": "VO", "3": "VI"}}
for (r, pn), fn in pinfn.items():
    e = EXP.get(r[0], {}).get(pn)
    if r.startswith("GDT"): continue
    if e and fn != e: bad(f"schematic pin function {r}.{pn} = {fn!r}, expected {e}")
print(f"schematic pins checked: {len(schnet)}")

# ---------- 5. PCB pad nets vs schematic
import pcbnew
b = pcbnew.LoadBoard("hfmc.kicad_pcb")
npads = 0
for fp in b.GetFootprints():
    for pad in fp.Pads():
        if not pad.GetNumber(): continue
        npads += 1
        want = schnet.get((fp.GetReference(), pad.GetNumber()))
        if pad.GetNetname() != want: bad(f"PCB {fp.GetReference()}.{pad.GetNumber()}: {pad.GetNetname()} != schematic {want}")
print(f"PCB pads checked: {npads}")

# ---------- 6. what is deliberately not 1:1
unmapped_sim = sorted(k for k in elems if not WIRES.match(k) and k not in bysim)
extra_kicad = sorted(p["ref"] for p in design.P if not p.get("gen") and p["ref"] not in SUPPLY.values() and p["ref"] != "U1")
print("sim-only elements (sources, loads, behavioural regulator, ESR/loss models):", " ".join(unmapped_sim))
print("KiCad-only parts (connectors, protection, test points, holes, extra bypass):", " ".join(extra_kicad))
print("RESULT:", "PASS" if not fail else f"FAIL ({len(fail)})")
sys.exit(1 if fail else 0)
